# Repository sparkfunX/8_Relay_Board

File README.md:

SparkX 8 Relay Control Board
========================================

[*8 Relay Control Board (SPX-24475)*](https://www.sparkfun.com/products/24475)

A simple breakout for controlling 8 relays with logic level signals. Each relay channel is opto-isolated from its corresponding logic input, the inputs accept both 3V and 5V logic, and a status LED on each channel makes it easy to tell at a glance which relay is energized. All LEDs on the board, including the power indicator, are connected through cuttable solder jumpers so they can be disabled if you don't need them. The relays are rated to 5A/250VAC, making them useful for a lot of power control applications.

Repository Contents
-------------------

* **/Hardware** - Eagle design files (.brd, .sch)
* **/Production** - Production panel files (.brd)

License Information
-------------------

This product is _**open source**_! 

Please review the LICENSE.md file for license information. 

If you have any questions or concerns on licensing, please contact technical support on our [SparkFun forums](https://forum.sparkfun.com/viewforum.php?f=152).

Distributed as-is; no warranty is given.

- Your friends at SparkFun.

_<COLLABORATION CREDIT>_

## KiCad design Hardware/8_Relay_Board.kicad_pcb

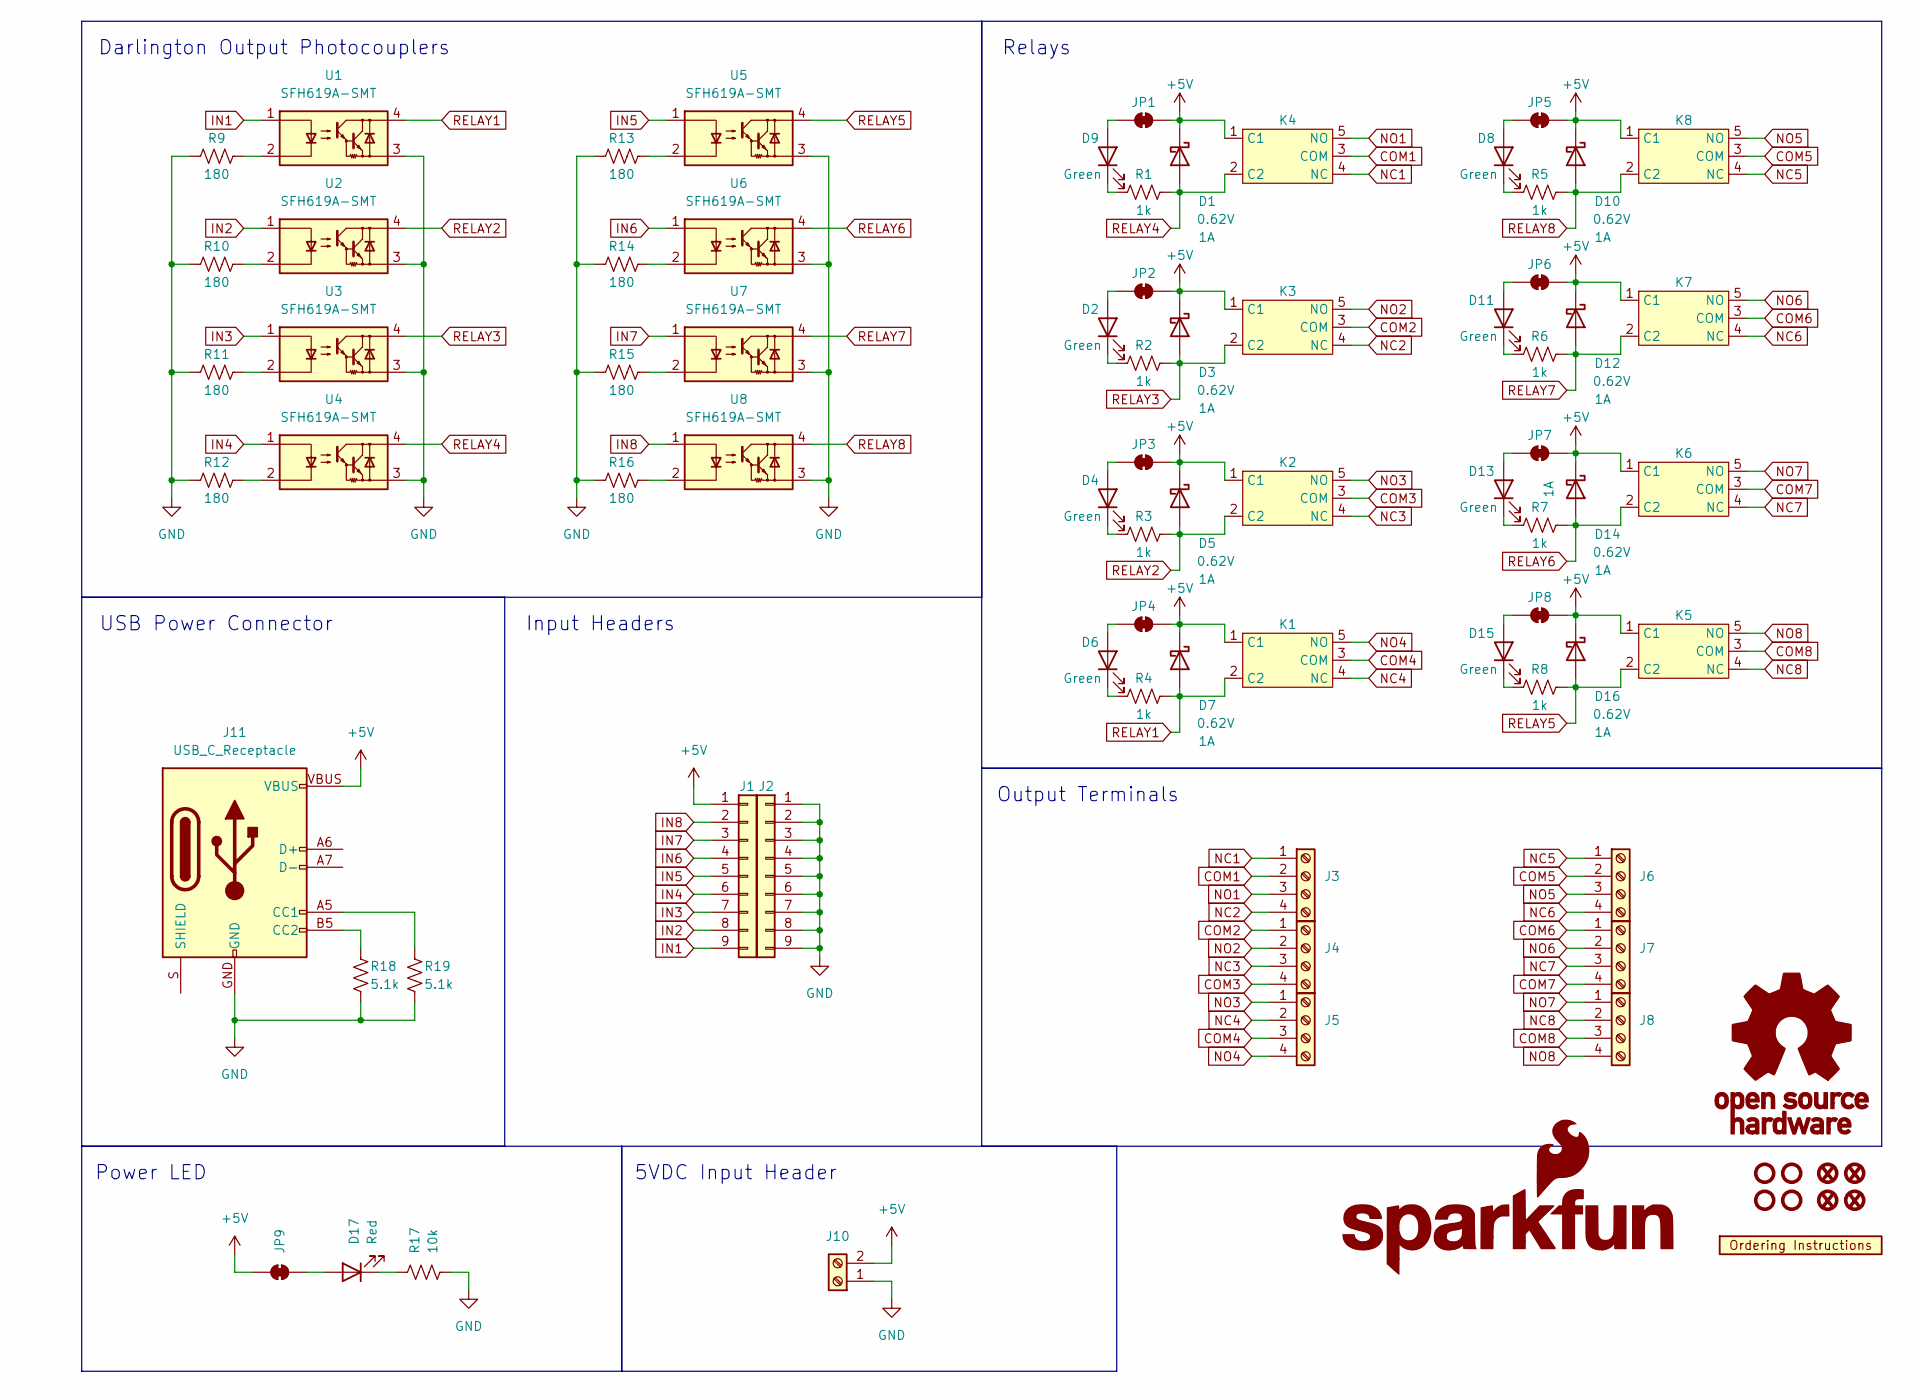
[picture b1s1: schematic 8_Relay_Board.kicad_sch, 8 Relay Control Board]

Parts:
D1, D3, D5, D7, D10, D12, D16: D_Schottky_1A_23V_0.62V; SOD-323
D2, D4, D6, D8, D9, D11, D13, D15: Green; LED_0603_1608Metric
D14: D_Schottky_1A_23V_0.62V; SOD-323; Reverse Voltage 23V
D17: Red; LED_0603_1608Metric
FID1, FID2, FID3, FID4: Fiducial_0.5; Fiducial_0.5mm_Mask1mm
G1: OSHW_Logo; Creative_Commons_License
G5: SparkFun_Logo; SparkFun_Logo_8mm
J1, J2: Conn_01x09; 1X09
J3, J4, J5, J6, J7, J8: Screw_Terminal_3.5mm_4; SCREWTERMINAL-3.5MM-4
J10: Screw_Terminal_3.5mm_2; SCREWTERMINAL-3.5MM-2
J11: USB_C_Receptacle; USB-C-16P
JP1, JP2, JP3, JP4, JP5, JP6, JP7, JP8, JP9: SMT-JUMPER_2_NC_TRACE_SILK
K1, K2, K3, K4, K5, K6, K7, K8: RELAY-JZC-11F
R1, R2, R3, R4, R5, R6, R7, R8: 1k; R_0603_1608Metric
R9, R10, R11, R12, R13, R14, R15, R16: 180; R_0603_1608Metric
R17: 10k; R_0603_1608Metric
R18, R19: 5.1k; R_0603_1608Metric
ST1, ST2, ST3, ST4: Stand_off; STAND-OFF
U1, U2, U3, U4, U5, U6, U7, U8: SFH619A-SMT; SMDIP4-WIDE
U9: ORDERING_INSTRUCTIONS

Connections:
+5V: D1.C, D3.C, D5.C, D7.C, D10.C, D12.C, D14.C, D16.C, J1.1, J10.2, J11.VBUS, JP1.2 (B), JP2.2 (B), JP3.2 (B), JP4.2 (B), JP5.2 (B), JP6.2 (B), JP7.2 (B), JP8.2 (B), JP9.2 (B), K1.1 (C1), K2.1 (C1), K3.1 (C1), K4.1 (C1), K5.1 (C1), K6.1 (C1), K7.1 (C1), K8.1 (C1)
COM1: J3.2, K4.3 (COM)
COM2: J4.1, K3.3 (COM)
COM3: J4.4, K2.3 (COM)
COM4: J5.3, K1.3 (COM)
COM5: J6.2, K8.3 (COM)
COM6: J7.1, K7.3 (COM)
COM7: J7.4, K6.3 (COM)
COM8: J8.3, K5.3 (COM)
GND: J2.1, J2.2, J2.3, J2.4, J2.5, J2.6, J2.7, J2.8, J2.9, J10.1, J11.GND, R9.1, R10.1, R11.1, R12.1, R13.1, R14.1, R15.1, R16.1, R17.2, R18.2, R19.2, U1.3, U2.3, U3.3, U4.3, U5.3, U6.3, U7.3, U8.3
IN1: J1.9, U1.1
IN2: J1.8, U2.1
IN3: J1.7, U3.1
IN4: J1.6, U4.1
IN5: J1.5, U5.1
IN6: J1.4, U6.1
IN7: J1.3, U7.1
IN8: J1.2, U8.1
NC1: J3.1, K4.4 (NC)
NC2: J3.4, K3.4 (NC)
NC3: J4.3, K2.4 (NC)
NC4: J5.2, K1.4 (NC)
NC5: J6.1, K8.4 (NC)
NC6: J6.4, K7.4 (NC)
NC7: J7.3, K6.4 (NC)
NC8: J8.2, K5.4 (NC)
NO1: J3.3, K4.5 (NO)
NO2: J4.2, K3.5 (NO)
NO3: J5.1, K2.5 (NO)
NO4: J5.4, K1.5 (NO)
NO5: J6.3, K8.5 (NO)
NO6: J7.2, K7.5 (NO)
NO7: J8.1, K6.5 (NO)
NO8: J8.4, K5.5 (NO)
unnamed: D2.2 (A), JP2.1 (A)
unnamed: D2.1 (K), R2.1
unnamed: D4.2 (A), JP3.1 (A)
unnamed: D4.1 (K), R3.1
unnamed: D6.2 (A), JP4.1 (A)
unnamed: D6.1 (K), R4.1
unnamed: D8.2 (A), JP5.1 (A)
unnamed: D8.1 (K), R5.1
unnamed: D9.2 (A), JP1.1 (A)
unnamed: D9.1 (K), R1.1
unnamed: D11.2 (A), JP6.1 (A)
unnamed: D11.1 (K), R6.1
unnamed: D13.2 (A), JP7.1 (A)
unnamed: D13.1 (K), R7.1
unnamed: D15.2 (A), JP8.1 (A)
unnamed: D15.1 (K), R8.1
unnamed: D17.2 (A), JP9.1 (A)
unnamed: D17.1 (K), R17.1
unnamed: J11.A5 (CC1), R19.1
unnamed: J11.B5 (CC2), R18.1
unnamed: J11.A6 (D+), J11.B6 (D+)
unnamed: J11.A7 (D-), J11.B7 (D-)
unnamed: R9.2, U1.2
unnamed: R10.2, U2.2
unnamed: R11.2, U3.2
unnamed: R12.2, U4.2
unnamed: R13.2, U5.2
unnamed: R14.2, U6.2
unnamed: R15.2, U7.2
unnamed: R16.2, U8.2
RELAY1: D7.A, K1.2 (C2), R4.2, U1.4
RELAY2: D5.A, K2.2 (C2), R3.2, U2.4
RELAY3: D3.A, K3.2 (C2), R2.2, U3.4
RELAY4: D1.A, K4.2 (C2), R1.2, U4.4
RELAY5: D16.A, K5.2 (C2), R8.2, U5.4
RELAY6: D14.A, K6.2 (C2), R7.2, U6.4
RELAY7: D12.A, K7.2 (C2), R6.2, U7.4
RELAY8: D10.A, K8.2 (C2), R5.2, U8.4

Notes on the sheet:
Relays
USB Power Connector
Output Terminals
Input Headers
5VDC Input Header
Power LED
Darlington Output Photocouplers

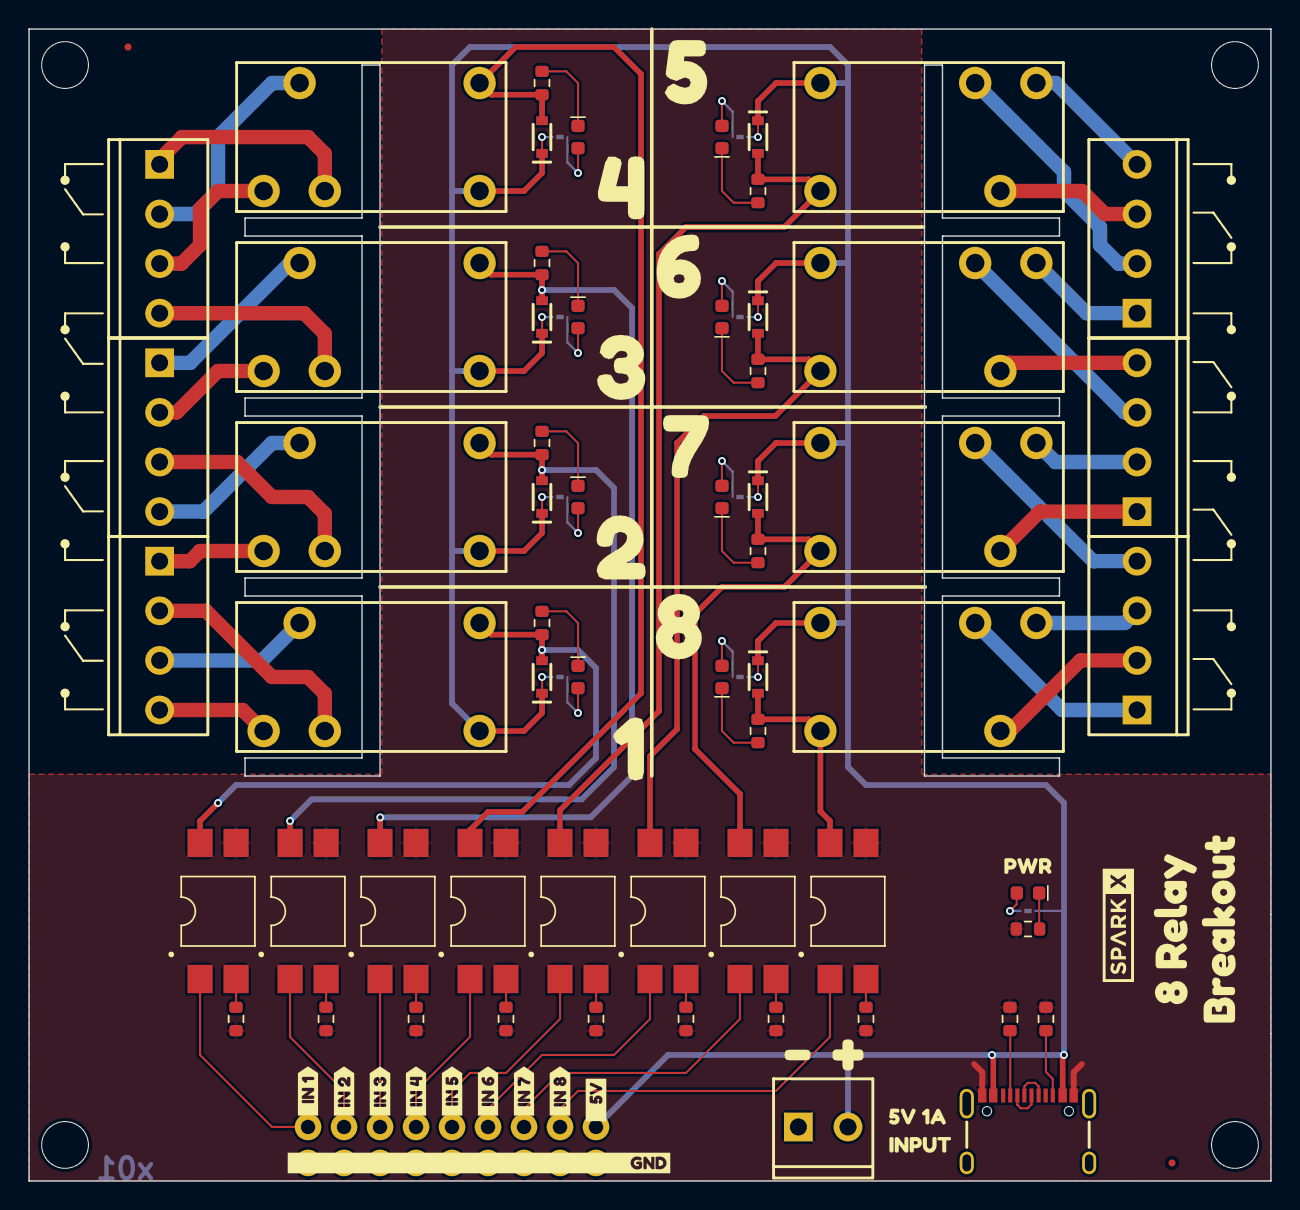
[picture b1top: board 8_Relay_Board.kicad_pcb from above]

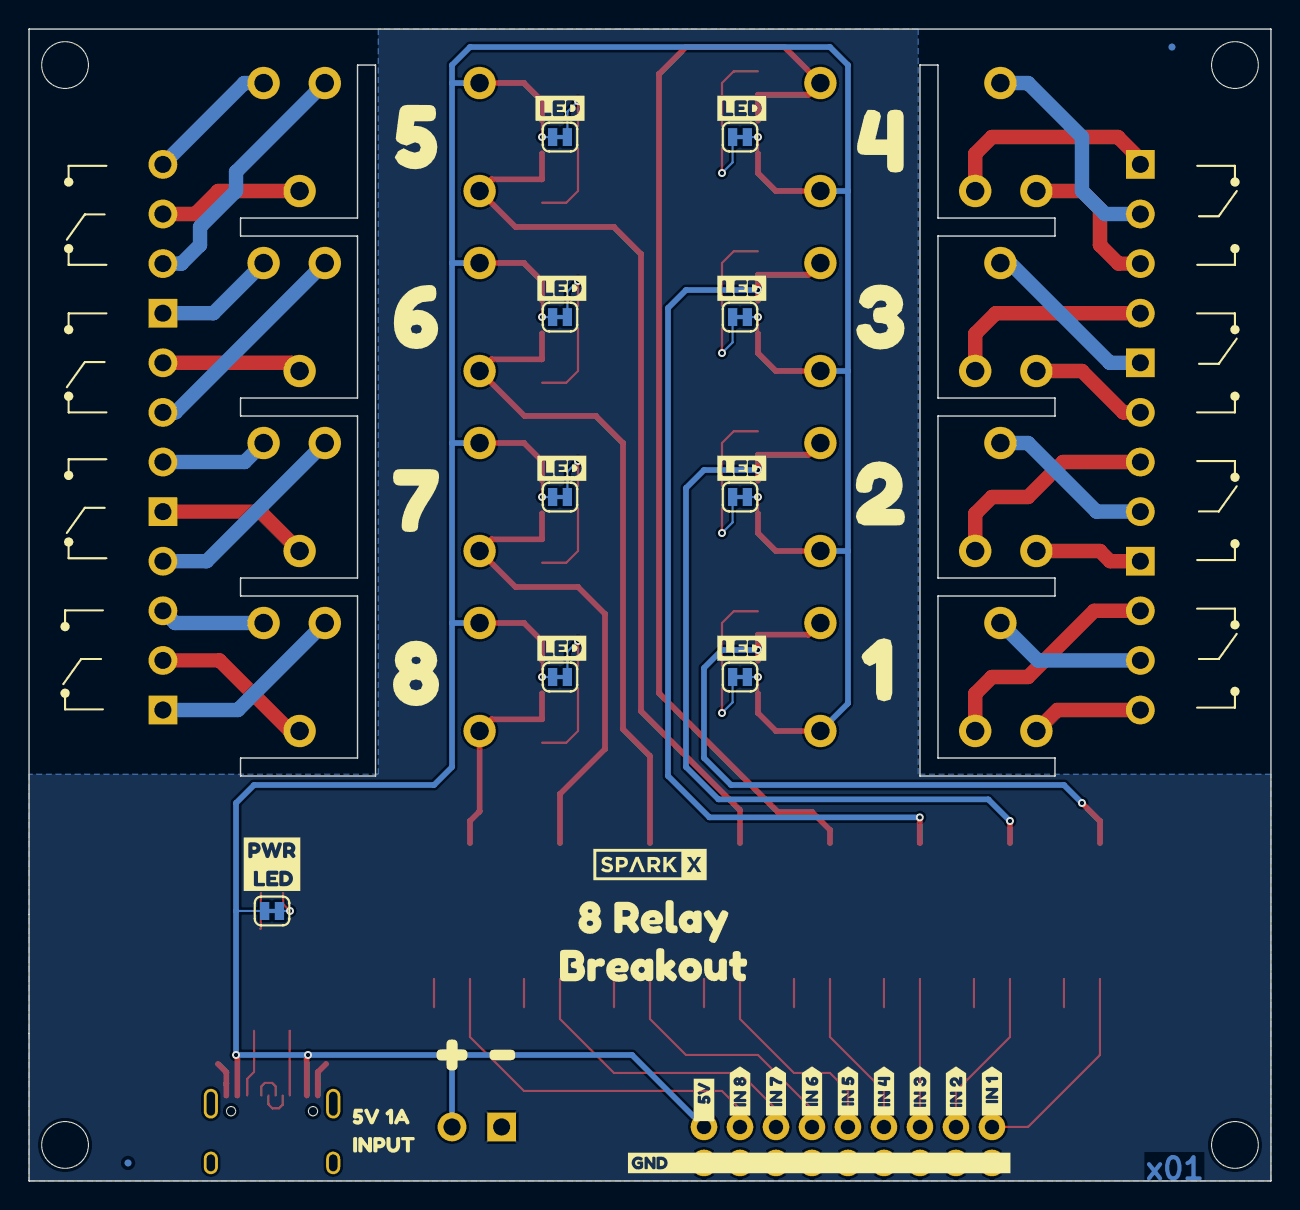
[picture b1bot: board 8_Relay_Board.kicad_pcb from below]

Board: 4 copper layers, 87.6 x 81.3 mm, 137 parts (43 on the bottom side), 72 nets.

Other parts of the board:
kibuzzard-652EF88E: G***; kibuzzard-652EF88E
kibuzzard-652EF841: G***; kibuzzard-652EF841
kibuzzard-652EF889: G***; kibuzzard-652EF889
kibuzzard-65656C10: G***; kibuzzard-65656C10
kibuzzard-65656C50: G***; kibuzzard-65656C50
kibuzzard-65656C62, kibuzzard-65656C62#2, kibuzzard-65656C62#3, kibuzzard-65656C62#4, kibuzzard-65656C62#5, kibuzzard-65656C62#6, kibuzzard-65656C62#7, kibuzzard-65656C62#8: G***; kibuzzard-65656C62
kibuzzard-652971A7, kibuzzard-652971A7#2: G***; kibuzzard-652971A7
kibuzzard-652971AD, kibuzzard-652971AD#2: G***; kibuzzard-652971AD
kibuzzard-652971B3, kibuzzard-652971B3#2: G***; kibuzzard-652971B3
kibuzzard-652973B2: G***; kibuzzard-652973B2
kibuzzard-652991A0: G***; kibuzzard-652991A0
kibuzzard-652997F8: G***; kibuzzard-652997F8
kibuzzard-6529717D, kibuzzard-6529717D#2: G***; kibuzzard-6529717D
kibuzzard-6529732E, kibuzzard-6529732E#2: G***; kibuzzard-6529732E
kibuzzard-6529733E, kibuzzard-6529733E#2: G***; kibuzzard-6529733E
kibuzzard-6529734A: G***; kibuzzard-6529734A
kibuzzard-6529980A: G***; kibuzzard-6529980A
kibuzzard-65297156, kibuzzard-65297156#2: G***; kibuzzard-65297156
kibuzzard-65297163, kibuzzard-65297163#2: G***; kibuzzard-65297163
kibuzzard-65297189, kibuzzard-65297189#2: G***; kibuzzard-65297189
kibuzzard-65297199, kibuzzard-65297199#2: G***; kibuzzard-65297199
kibuzzard-65297316, kibuzzard-65297316#2: G***; kibuzzard-65297316
kibuzzard-65297321, kibuzzard-65297321#2: G***; kibuzzard-65297321
kibuzzard-65297327, kibuzzard-65297327#2: G***; kibuzzard-65297327
kibuzzard-65297338, kibuzzard-65297338#2: G***; kibuzzard-65297338
kibuzzard-65297343, kibuzzard-65297343#2: G***; kibuzzard-65297343
kibuzzard-65297353, kibuzzard-65297353#2: G***; kibuzzard-65297353
kibuzzard-65297443, kibuzzard-65297443#2: G***; kibuzzard-65297443
kibuzzard-65297450, kibuzzard-65297450#2: G***; kibuzzard-65297450
kibuzzard-65299803: G***; kibuzzard-65299803
kibuzzard-65299816: G***; kibuzzard-65299816

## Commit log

2023-10-09 Schematic and Airwire
2023-10-10 Close to finishing layout
2023-10-13 Ready for final review
2023-12-19 Second pre-release revision
    - Add isolation under relays
2024-06-11 Add docs zip and schematic pdf
2024-06-11 Housekeeping

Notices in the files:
parts and their libraries:
Released under the Creative Commons Attribution Share-Alike 4.0 License
https://creativecommons.org/licenses/by-sa/4.0
